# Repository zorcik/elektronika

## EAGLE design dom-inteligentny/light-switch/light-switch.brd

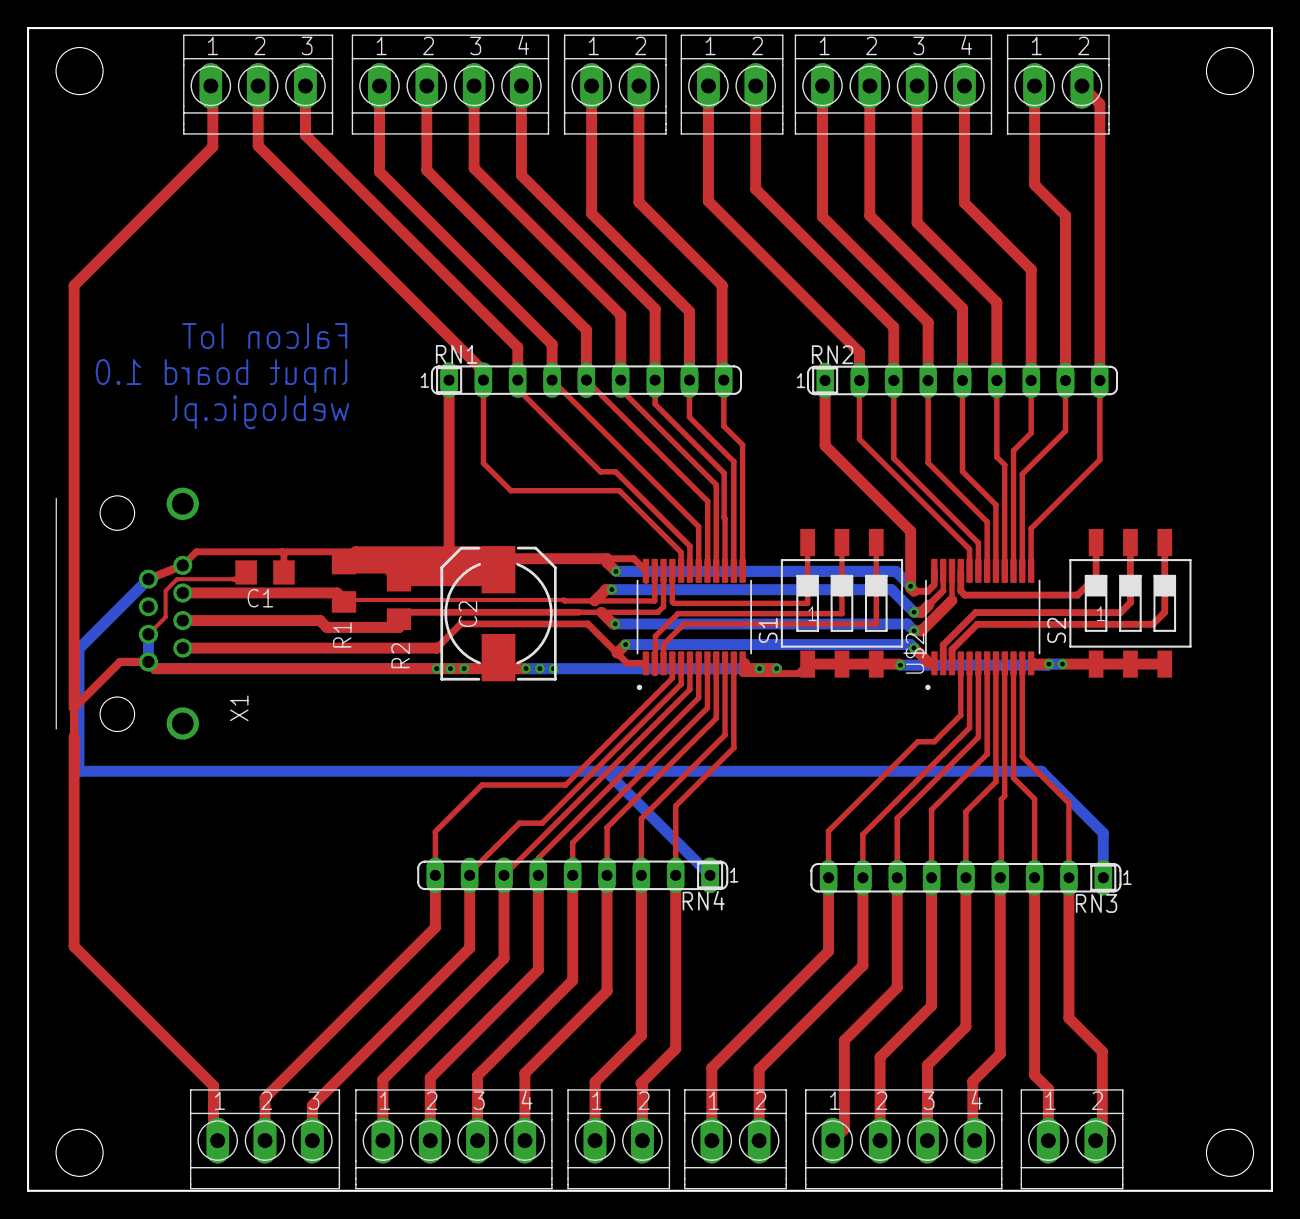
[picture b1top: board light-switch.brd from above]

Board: 2 copper layers, 92.0 x 86.0 mm, 25 parts (0 on the bottom side), 43 nets.

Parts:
C1: C1206
C2: 150CLZ-0810
R1, R2: R1206
RN1, RN2, RN3, RN4: SIL9
S1, S2: SWS003; SMS-003
U$1, U$2: PCF8575CSSOP24; SOP65P775X200-24N
X1: GLX-S-88M
X2, X3: TERMINAL-BLOCK-3.5MM-3-PIN-LONG-PAD; TERMINAL-BLOCK-3-PIN-3.5MM-LONG-PAD
X4, X6, X10, X11: TERMINAL-BLOCK-3.5MM-4-PIN-LONG-PAD; TERMINAL-BLOCK-4-PIN-3.5MM-LONG-PAD
X5, X7, X8, X9, X12, X13: TERMINAL-BLOCK-3.5MM-2-PIN-LONG-PAD; TERMINAL-BLOCK-2-PIN-3.5MM-LONG-PAD

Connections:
GND: C1.1, C2.-, S1.1, S1.2, S1.3, S2.1, S2.2, S2.3, U$1.12, U$2.12, X1.1, X1.3, X2.1, X3.1
INT: U$1.1, U$2.1, X1.2
unnamed: RN1.2, U$1.20, X3.2
unnamed: RN1.3, U$1.19, X3.3
unnamed: RN1.4, U$1.18, X4.1
unnamed: RN1.5, U$1.17, X4.2
unnamed: RN1.6, U$1.16, X4.3
unnamed: RN1.7, U$1.15, X4.4
unnamed: RN1.8, U$1.14, X5.1
unnamed: RN1.9, U$1.13, X5.2
unnamed: RN4.9, U$1.4, X2.2
unnamed: RN4.8, U$1.5, X2.3
unnamed: RN4.7, U$1.6, X6.1
unnamed: RN4.6, U$1.7, X6.2
unnamed: RN4.5, U$1.8, X6.3
unnamed: RN4.4, U$1.9, X6.4
unnamed: RN4.3, U$1.10, X7.1
unnamed: RN4.2, U$1.11, X7.2
unnamed: RN3.9, U$2.4, X9.1
unnamed: S1.4, U$1.3
unnamed: S2.5, U$2.2
unnamed: S1.6, U$1.21
unnamed: S1.5, U$1.2
unnamed: S2.4, U$2.3
unnamed: RN2.2, U$2.20, X8.1
unnamed: RN2.3, U$2.19, X8.2
unnamed: RN2.4, U$2.18, X10.1
unnamed: RN2.5, U$2.17, X10.2
unnamed: RN2.6, U$2.16, X10.3
unnamed: RN2.7, U$2.15, X10.4
unnamed: RN2.8, U$2.14, X12.1
unnamed: RN2.9, U$2.13, X12.2
unnamed: RN3.8, U$2.5, X9.2
unnamed: RN3.7, U$2.6, X11.1
unnamed: RN3.6, U$2.7, X11.2
unnamed: RN3.5, U$2.8, X11.3
unnamed: RN3.4, U$2.9, X11.4
unnamed: RN3.3, U$2.10, X13.1
unnamed: RN3.2, U$2.11, X13.2
unnamed: S2.6, U$2.21
SCL: R2.1, U$1.22, U$2.22, X1.4
SDA: R1.1, U$1.23, U$2.23, X1.6
VDD: C1.2, C2.+, R1.2, R2.2, RN1.1, RN2.1, RN3.1, RN4.1, U$1.24, U$2.24, X1.7, X1.8

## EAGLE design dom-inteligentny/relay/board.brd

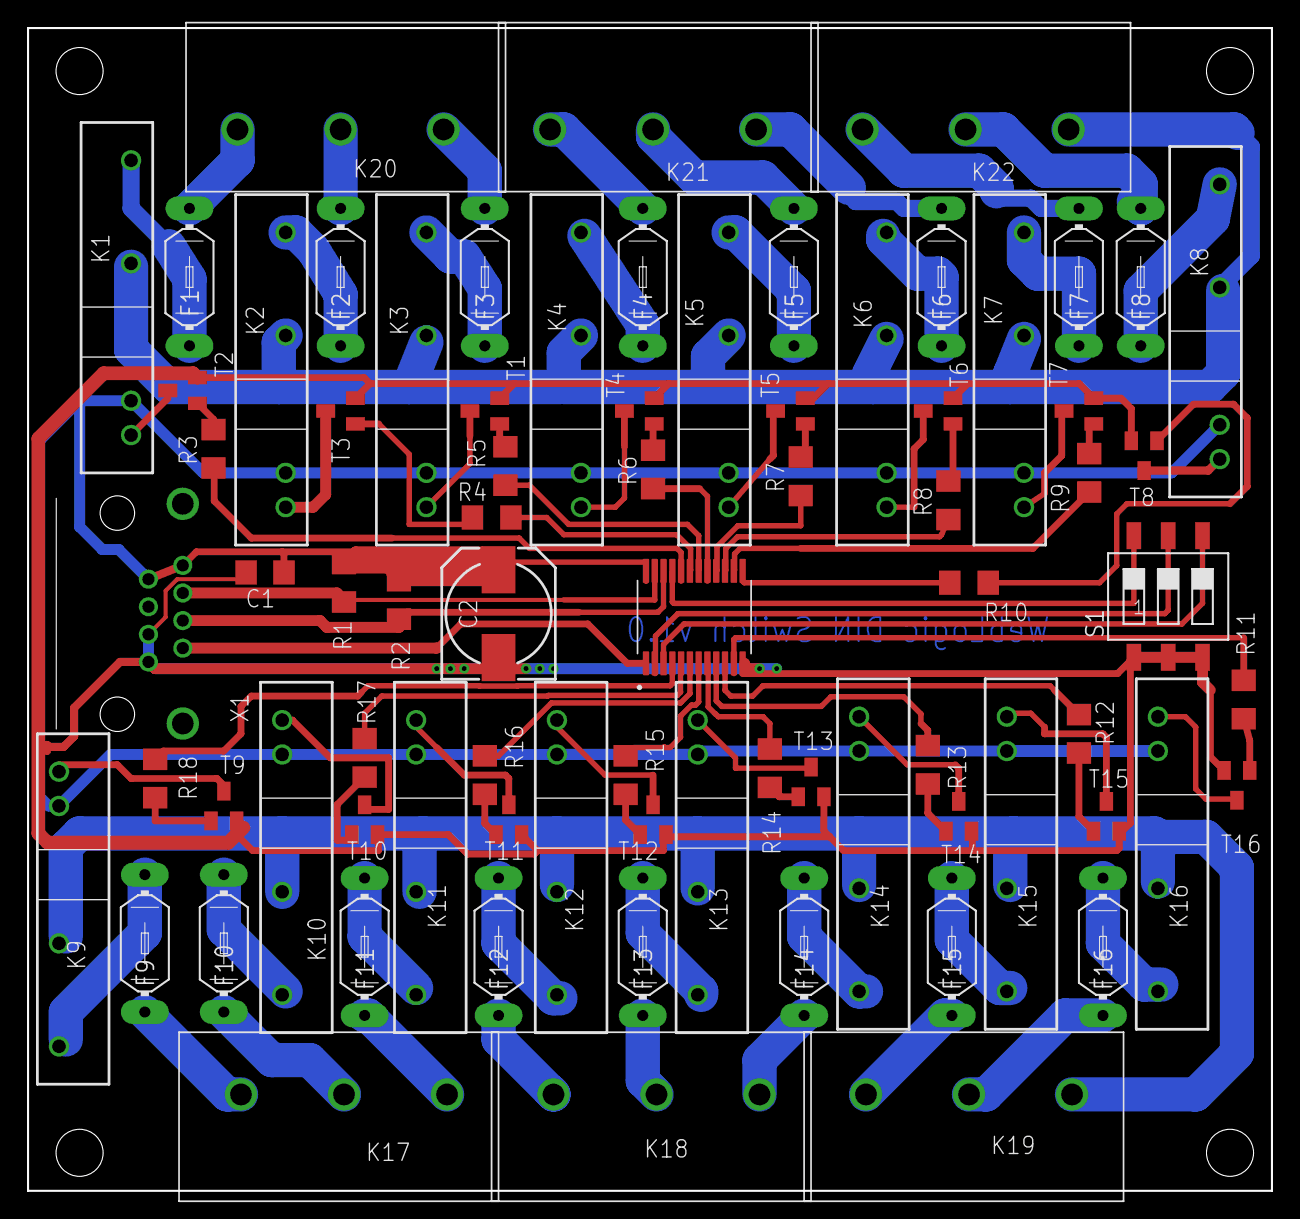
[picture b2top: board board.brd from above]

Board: 2 copper layers, 92.0 x 86.0 mm, 77 parts (0 on the bottom side), 90 nets.

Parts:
C1: C1206
C2: 150CLZ-0810
F1, F2, F3, F4, F5, F6, F7, F8, F9, F10, F11, F12, F13, F14, F15, F16: FUSELITTLEFUSE; LITTLEFUSE
K1, K2, K3, K4, K5, K6, K7, K8, K9, K10, K11, K12, K13, K14, K15, K16: OMRON-G3MB-202P-SSR
K17, K18, K19, K20, K21, K22: 691218410003
R1, R2, R3, R4, R5, R6, R7, R8, R9, R10, R11, R12, R13, R14, R15, R16, R17, R18: R1206
S1: SWS003; SMS-003
T1, T2, T3, T4, T5, T6, T7, T8, T9, T10, T11, T12, T13, T14, T15, T16: BC847; SOT23
U$1: PCF8575CSSOP24; SOP65P775X200-24N
X1: GLX-S-88M

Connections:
GND: C1.1, C2.-, S1.1, S1.2, S1.3, T1.2, T2.2, T3.2, T4.2, T5.2, T6.2, T7.2, T8.2, T9.2, T10.2, T11.2, T12.2, T13.2, T14.2, T15.2, T16.2, U$1.12, X1.1, X1.3
unnamed: F16.2, K16.1
unnamed: U$1.1, X1.2
unnamed: R3.1, U$1.20
unnamed: R4.1, U$1.19
unnamed: R18.2, T9.1
unnamed: R5.1, U$1.18
unnamed: R6.1, U$1.17
unnamed: R7.1, U$1.16
unnamed: R8.1, U$1.15
unnamed: R9.1, U$1.14
unnamed: R10.1, U$1.13
unnamed: R11.1, U$1.11
unnamed: R12.1, U$1.10
unnamed: R13.1, U$1.9
unnamed: R14.1, U$1.8
unnamed: R15.1, U$1.7
unnamed: R16.1, U$1.6
unnamed: R17.1, U$1.5
unnamed: R2.1, U$1.22, X1.4
unnamed: S1.4, U$1.3
unnamed: R1.1, U$1.23, X1.6
unnamed: K9.2, K10.2, K11.2, K12.2, K13.2, K14.2, K15.2, K16.2, K19.3
unnamed: F13.2, K13.1
unnamed: F14.1, K18.3
unnamed: F10.1, K17.2
unnamed: F11.1, K17.3
unnamed: S1.6, U$1.21
unnamed: S1.5, U$1.2
unnamed: C1.2, C2.+, K1.3, K2.3, K3.3, K4.3, K5.3, K6.3, K7.3, K8.3, K9.3, K10.3, K11.3, K12.3, K13.3, K14.3, K15.3, K16.3, R1.2, R2.2, U$1.24, X1.7, X1.8
unnamed: F9.1, K17.1
unnamed: F1.1, K1.1
unnamed: F2.1, K2.1
unnamed: F12.1, K18.1
unnamed: F3.1, K3.1
unnamed: F4.1, K4.1
unnamed: F15.1, K19.1
unnamed: F5.1, K5.1
unnamed: K1.2, K2.2, K3.2, K4.2, K5.2, K6.2, K7.2, K8.2, K22.1
unnamed: F8.2, K22.2
unnamed: F7.2, K22.3
unnamed: F6.2, K21.1
unnamed: F5.2, K21.2
unnamed: F4.2, K21.3
unnamed: F3.2, K20.1
unnamed: F6.1, K6.1
unnamed: F1.2, K20.3
unnamed: F7.1, K7.1
unnamed: F8.1, K8.1
unnamed: F9.2, K9.1
unnamed: F2.2, K20.2
unnamed: F10.2, K10.1
unnamed: F11.2, K11.1
unnamed: F12.2, K12.1
unnamed: F14.2, K14.1
unnamed: F15.2, K15.1
unnamed: F16.1, K19.2
unnamed: F13.1, K18.2
unnamed: R18.1, U$1.4
unnamed: R3.2, T2.1
unnamed: K1.4, T2.3
unnamed: R4.2, T3.1
unnamed: K2.4, T3.3
unnamed: R5.2, T1.1
unnamed: R6.2, T4.1
unnamed: R7.2, T5.1
unnamed: R8.2, T6.1
unnamed: R9.2, T7.1
unnamed: R10.2, T8.1
unnamed: K8.4, T8.3
unnamed: K7.4, T7.3
unnamed: K6.4, T6.3
unnamed: K5.4, T5.3
unnamed: R17.2, T10.1
unnamed: K4.4, T4.3
unnamed: K3.4, T1.3
unnamed: K9.4, T9.3
unnamed: K10.4, T10.3
unnamed: K11.4, T11.3
unnamed: R16.2, T11.1
unnamed: R11.2, T16.1
unnamed: R12.2, T15.1
unnamed: R13.2, T14.1
unnamed: R14.2, T13.1
unnamed: R15.2, T12.1
unnamed: K16.4, T16.3
unnamed: K15.4, T15.3
unnamed: K14.4, T14.3
unnamed: K13.4, T13.3
unnamed: K12.4, T12.3

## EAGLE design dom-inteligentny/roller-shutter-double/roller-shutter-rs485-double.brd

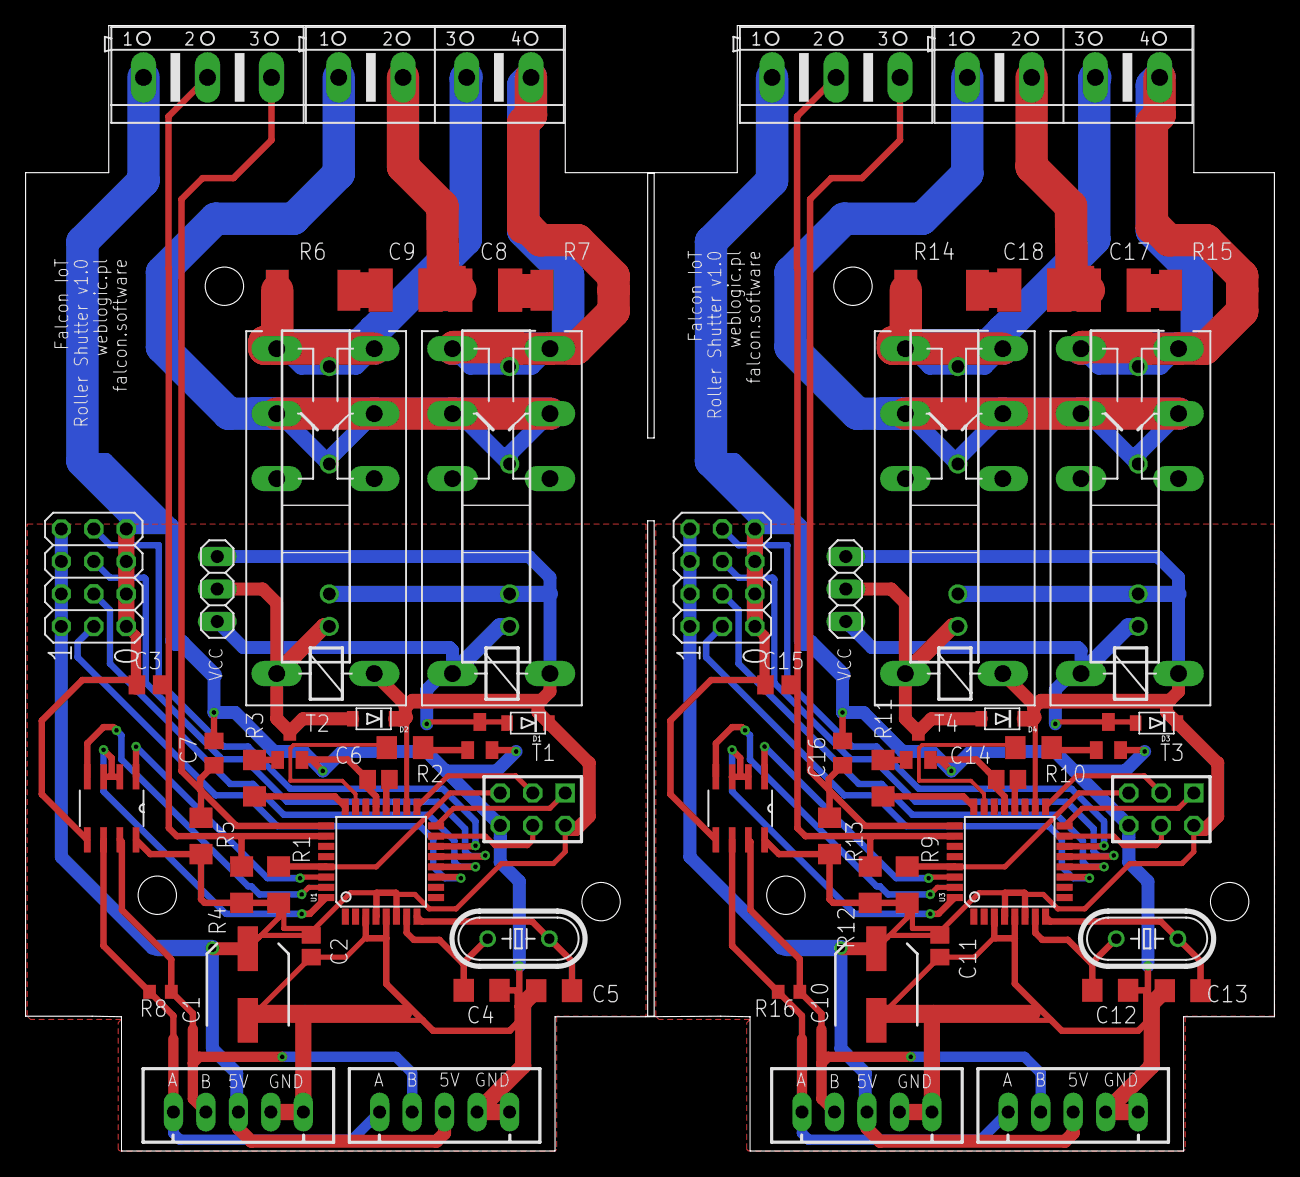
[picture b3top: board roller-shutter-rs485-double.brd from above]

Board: 2 copper layers, 97.6 x 88.0 mm, 70 parts (0 on the bottom side), 64 nets.

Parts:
C1, C10: SANYO-OSCON_SMD_C6
C2, C6, C11, C14: 0.1uF; C0805
C3, C7, C15, C16: C0805
C4, C5, C12, C13: 22pF; C1206
C8, C9, C17, C18: C1812
D1, D2, D3, D4: SOD-123FL
JP1, JP3: AVR-ISP-6
JP2, JP4: 1X03
JP5, JP6: 3X04
K1, K4, K5, K6: RP421110; RP420
K2, K3, K7, K8: OMRON-G3MB-202P-SSR
Q1, Q2: 16MHz; HC49/S
R1, R9: 10K; R1206
R2, R3, R4, R5, R10, R11, R12, R13: R1206
R6, R7, R14, R15: R2512
R8, R16: 120R; R0603
T1, T2, T3, T4: BC847; SOT23
U1, U3: ATMEGA328; TQFP32-08
U2, U4: MAX487ESA+TCBX; SOIC127P600X175-8N
X1, X2, X3, X6: JST-XH-05-PIN-LONG-PAD; JST-XH-05-PACKAGE-LONG-PAD
X4, X7: AK500/3
X5, X8: AK500/4

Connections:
A: R8.2, U2.6, X2.1, X3.1
A0: R2.1, U1.23
A1: R3.1, U1.24
A2: C7.2, R5.1, U1.25, X4.3
A3: C3.2, R4.1, U1.26, X4.2
A4: R10.1, U3.23
A5: R11.1, U3.24
A8: C16.2, R13.1, U3.25, X7.3
A9: C15.2, R12.1, U3.26, X7.2
A12: R16.2, U4.6, X1.1, X6.1
AREF: C6.1, U1.20
AREF1: C14.1, U3.20
B: R8.1, U2.7, X2.2, X3.2
B1: R16.1, U4.7, X1.2, X6.2
D0: U1.30, U2.1
D1: U1.31, U2.4
D2: U1.32, U2.2, U2.3
D7: JP6.11, U1.11
D8: JP6.8, U1.12
D9: JP6.5, U1.13
D10: JP6.2, U1.14
D11: JP1.4, U1.15
D12: JP1.1, U1.16
D13: JP1.3, U1.17
D14: U3.30, U4.1
D15: U3.31, U4.4
D16: U3.32, U4.2, U4.3
D21: JP5.11, U3.11
D22: JP5.8, U3.12
D23: JP5.5, U3.13
D24: JP5.2, U3.14
D25: JP3.4, U3.15
D26: JP3.1, U3.16
D27: JP3.3, U3.17
GND: C1.-, C2.2, C3.1, C4.2, C5.2, C6.2, C7.1, JP1.6, JP6.3, JP6.6, JP6.9, JP6.12, T1.2, T2.2, U1.3, U1.5, U1.21, U2.5, X2.4, X2.5, X3.4, X3.5, X4.1
GND1: C10.-, C11.2, C12.2, C13.2, C14.2, C15.1, C16.1, JP3.6, JP5.3, JP5.6, JP5.9, JP5.12, T3.2, T4.2, U3.3, U3.5, U3.21, U4.5, X1.4, X1.5, X6.4, X6.5, X7.1
unnamed: D1.A, JP2.1, K1.A2, K2.4, T1.3
unnamed: D2.A, JP2.2, K3.4, K4.A2, T2.3
unnamed: C12.1, Q2.2, U3.7
unnamed: K1.11, K1.21, K2.2, K3.2, K4.11, K4.21, X5.1
unnamed: R2.2, T1.1
unnamed: R3.2, T2.1
unnamed: K1.14, K1.24, K2.1, R7.2, X5.4
unnamed: K3.1, K4.14, K4.24, R6.2, X5.3
unnamed: C8.2, R7.1
unnamed: C9.2, R6.1
unnamed: C8.1, C9.1, X5.2
unnamed: C13.1, Q2.1, U3.8
unnamed: D3.A, JP4.1, K5.A2, K7.4, T3.3
unnamed: D4.A, JP4.2, K6.A2, K8.4, T4.3
unnamed: R10.2, T3.1
unnamed: R11.2, T4.1
unnamed: K5.11, K5.21, K6.11, K6.21, K7.2, K8.2, X8.1
unnamed: K5.14, K5.24, K7.1, R15.2, X8.4
unnamed: K6.14, K6.24, K8.1, R14.2, X8.3
unnamed: C17.2, R15.1
unnamed: C18.2, R14.1
unnamed: C17.1, C18.1, X8.2
unnamed: C4.1, Q1.2, U1.7
unnamed: C5.1, Q1.1, U1.8
RST: JP1.5, R1.1, U1.29
RST1: JP3.5, R9.1, U3.29
VCC: C1.+, C2.1, D1.C, D2.C, JP1.2, JP2.3, JP6.1, JP6.4, JP6.7, JP6.10, K1.A1, K2.3, K3.3, K4.A1, R1.2, R4.2, R5.2, U1.4, U1.6, U1.18, U2.8, X2.3, X3.3
VCC1: C10.+, C11.1, D3.C, D4.C, JP3.2, JP4.3, JP5.1, JP5.4, JP5.7, JP5.10, K5.A1, K6.A1, K7.3, K8.3, R9.2, R12.2, R13.2, U3.4, U3.6, U3.18, U4.8, X1.3, X6.3

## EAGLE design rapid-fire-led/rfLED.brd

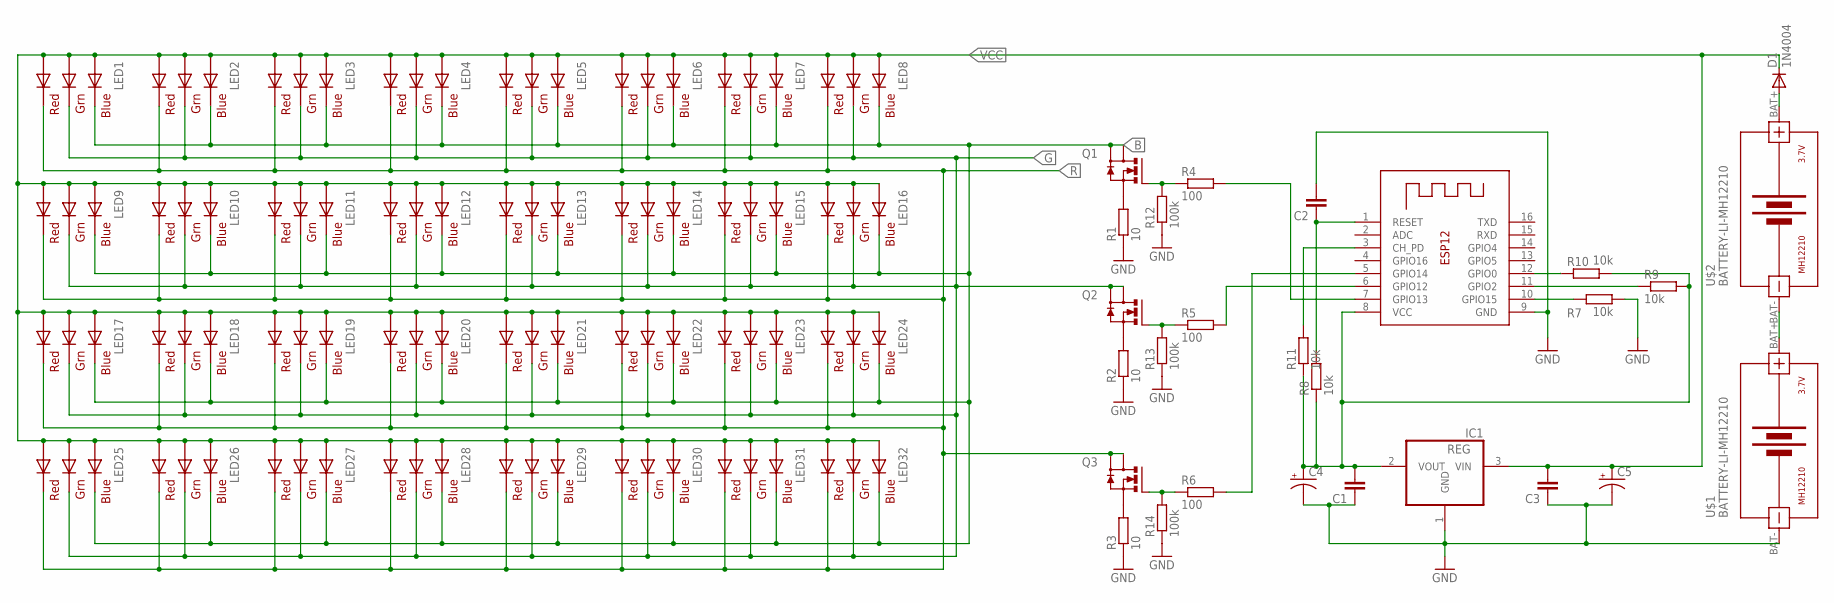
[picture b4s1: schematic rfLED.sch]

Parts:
C1, C2, C3: C; C0805
C4, C5: CPOL-US150CLZ-1010; 150CLZ-1010
D1: 1N4004; DO41-10
IC1: REG; SOT223
LED1, LED2, LED3, LED4, LED5, LED6, LED7, LED8, LED9, LED10, LED11, LED12, LED13, LED14, LED15, LED16, LED17, LED18, LED19, LED20, LED21, LED22, LED23, LED24, LED25, LED26, LED27, LED28, LED29, LED30, LED31, LED32: RGBLED5050
Q1, Q2, Q3: MOSFET_N_SOT223; SOT223
R1, R2, R3: 10; R2512
R4, R5, R6: 100; R1206
R7, R8, R9, R10, R11: 10k; R1206
R12, R13, R14: 100k; R1206
U$1, U$2: BATTERY-LI-MH12210
X1: ESP-12

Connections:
B: LED1.4 (BLUE_C), LED2.4 (BLUE_C), LED3.4 (BLUE_C), LED4.4 (BLUE_C), LED5.4 (BLUE_C), LED6.4 (BLUE_C), LED7.4 (BLUE_C), LED8.4 (BLUE_C), LED9.4 (BLUE_C), LED10.4 (BLUE_C), LED11.4 (BLUE_C), LED12.4 (BLUE_C), LED13.4 (BLUE_C), LED14.4 (BLUE_C), LED15.4 (BLUE_C), LED16.4 (BLUE_C), LED17.4 (BLUE_C), LED18.4 (BLUE_C), LED19.4 (BLUE_C), LED20.4 (BLUE_C), LED21.4 (BLUE_C), LED22.4 (BLUE_C), LED23.4 (BLUE_C), LED24.4 (BLUE_C), LED25.4 (BLUE_C), LED26.4 (BLUE_C), LED27.4 (BLUE_C), LED28.4 (BLUE_C), LED29.4 (BLUE_C), LED30.4 (BLUE_C), LED31.4 (BLUE_C), LED32.4 (BLUE_C), Q1.2 (D), Q1.4 (D1)
G: LED1.6 (GREEN_C), LED2.6 (GREEN_C), LED3.6 (GREEN_C), LED4.6 (GREEN_C), LED5.6 (GREEN_C), LED6.6 (GREEN_C), LED7.6 (GREEN_C), LED8.6 (GREEN_C), LED9.6 (GREEN_C), LED10.6 (GREEN_C), LED11.6 (GREEN_C), LED12.6 (GREEN_C), LED13.6 (GREEN_C), LED14.6 (GREEN_C), LED15.6 (GREEN_C), LED16.6 (GREEN_C), LED17.6 (GREEN_C), LED18.6 (GREEN_C), LED19.6 (GREEN_C), LED20.6 (GREEN_C), LED21.6 (GREEN_C), LED22.6 (GREEN_C), LED23.6 (GREEN_C), LED24.6 (GREEN_C), LED25.6 (GREEN_C), LED26.6 (GREEN_C), LED27.6 (GREEN_C), LED28.6 (GREEN_C), LED29.6 (GREEN_C), LED30.6 (GREEN_C), LED31.6 (GREEN_C), LED32.6 (GREEN_C), Q2.2 (D), Q2.4 (D1)
GND: C1.1, C2.2, C3.1, C4.-, C5.-, IC1.1 (GND), R1.1, R2.1, R3.1, R7.2, R12.1, R13.1, R14.1, U$1.BAT-, X1.9 (GND)
unnamed: Q1.3 (S), R1.2
unnamed: Q2.3 (S), R2.2
unnamed: Q3.3 (S), R3.2
unnamed: Q1.1 (G), R4.1, R12.2
unnamed: Q2.1 (G), R5.1, R13.2
unnamed: Q3.1 (G), R6.1, R14.2
unnamed: R5.2, X1.6 (GPIO12)
unnamed: C1.2, C4.+, IC1.2 (VOUT), R8.1, R9.2, R10.2, R11.1, X1.8 (VCC)
unnamed: R6.2, X1.5 (GPIO14)
unnamed: R4.2, X1.7 (GPIO13)
unnamed: R7.1, X1.10 (GPIO15)
unnamed: U$1.BAT+, U$2.BAT-
unnamed: C2.1, R8.2, X1.1 (RESET)
unnamed: R10.1, X1.12 (GPIO0)
unnamed: R9.1, X1.11 (GPIO2)
unnamed: D1.A, U$2.BAT+
unnamed: R11.2, X1.3 (CH_PD)
R: LED1.5 (RED_C), LED2.5 (RED_C), LED3.5 (RED_C), LED4.5 (RED_C), LED5.5 (RED_C), LED6.5 (RED_C), LED7.5 (RED_C), LED8.5 (RED_C), LED9.5 (RED_C), LED10.5 (RED_C), LED11.5 (RED_C), LED12.5 (RED_C), LED13.5 (RED_C), LED14.5 (RED_C), LED15.5 (RED_C), LED16.5 (RED_C), LED17.5 (RED_C), LED18.5 (RED_C), LED19.5 (RED_C), LED20.5 (RED_C), LED21.5 (RED_C), LED22.5 (RED_C), LED23.5 (RED_C), LED24.5 (RED_C), LED25.5 (RED_C), LED26.5 (RED_C), LED27.5 (RED_C), LED28.5 (RED_C), LED29.5 (RED_C), LED30.5 (RED_C), LED31.5 (RED_C), LED32.5 (RED_C), Q3.2 (D), Q3.4 (D1)
VCC: C3.2, C5.+, D1.C, IC1.3 (VIN), LED1.1 (GREEN_A), LED1.2 (RED_A), LED1.3 (BLUE_A), LED2.1 (GREEN_A), LED2.2 (RED_A), LED2.3 (BLUE_A), LED3.1 (GREEN_A), LED3.2 (RED_A), LED3.3 (BLUE_A), LED4.1 (GREEN_A), LED4.2 (RED_A), LED4.3 (BLUE_A), LED5.1 (GREEN_A), LED5.2 (RED_A), LED5.3 (BLUE_A), LED6.1 (GREEN_A), LED6.2 (RED_A), LED6.3 (BLUE_A), LED7.1 (GREEN_A), LED7.2 (RED_A), LED7.3 (BLUE_A), LED8.1 (GREEN_A), LED8.2 (RED_A), LED8.3 (BLUE_A), LED9.1 (GREEN_A), LED9.2 (RED_A), LED9.3 (BLUE_A), LED10.1 (GREEN_A), LED10.2 (RED_A), LED10.3 (BLUE_A), LED11.1 (GREEN_A), LED11.2 (RED_A), LED11.3 (BLUE_A), LED12.1 (GREEN_A), LED12.2 (RED_A), LED12.3 (BLUE_A), LED13.1 (GREEN_A), LED13.2 (RED_A), LED13.3 (BLUE_A), LED14.1 (GREEN_A), LED14.2 (RED_A), LED14.3 (BLUE_A), LED15.1 (GREEN_A), LED15.2 (RED_A), LED15.3 (BLUE_A), LED16.1 (GREEN_A), LED16.2 (RED_A), LED16.3 (BLUE_A), LED17.1 (GREEN_A), LED17.2 (RED_A), LED17.3 (BLUE_A), LED18.1 (GREEN_A), LED18.2 (RED_A), LED18.3 (BLUE_A), LED19.1 (GREEN_A), LED19.2 (RED_A), LED19.3 (BLUE_A), LED20.1 (GREEN_A), LED20.2 (RED_A), LED20.3 (BLUE_A), LED21.1 (GREEN_A), LED21.2 (RED_A), LED21.3 (BLUE_A), LED22.1 (GREEN_A), LED22.2 (RED_A), LED22.3 (BLUE_A), LED23.1 (GREEN_A), LED23.2 (RED_A), LED23.3 (BLUE_A), LED24.1 (GREEN_A), LED24.2 (RED_A), LED24.3 (BLUE_A), LED25.1 (GREEN_A), LED25.2 (RED_A), LED25.3 (BLUE_A), LED26.1 (GREEN_A), LED26.2 (RED_A), LED26.3 (BLUE_A), LED27.1 (GREEN_A), LED27.2 (RED_A), LED27.3 (BLUE_A), LED28.1 (GREEN_A), LED28.2 (RED_A), LED28.3 (BLUE_A), LED29.1 (GREEN_A), LED29.2 (RED_A), LED29.3 (BLUE_A), LED30.1 (GREEN_A), LED30.2 (RED_A), LED30.3 (BLUE_A), LED31.1 (GREEN_A), LED31.2 (RED_A), LED31.3 (BLUE_A), LED32.1 (GREEN_A), LED32.2 (RED_A), LED32.3 (BLUE_A)

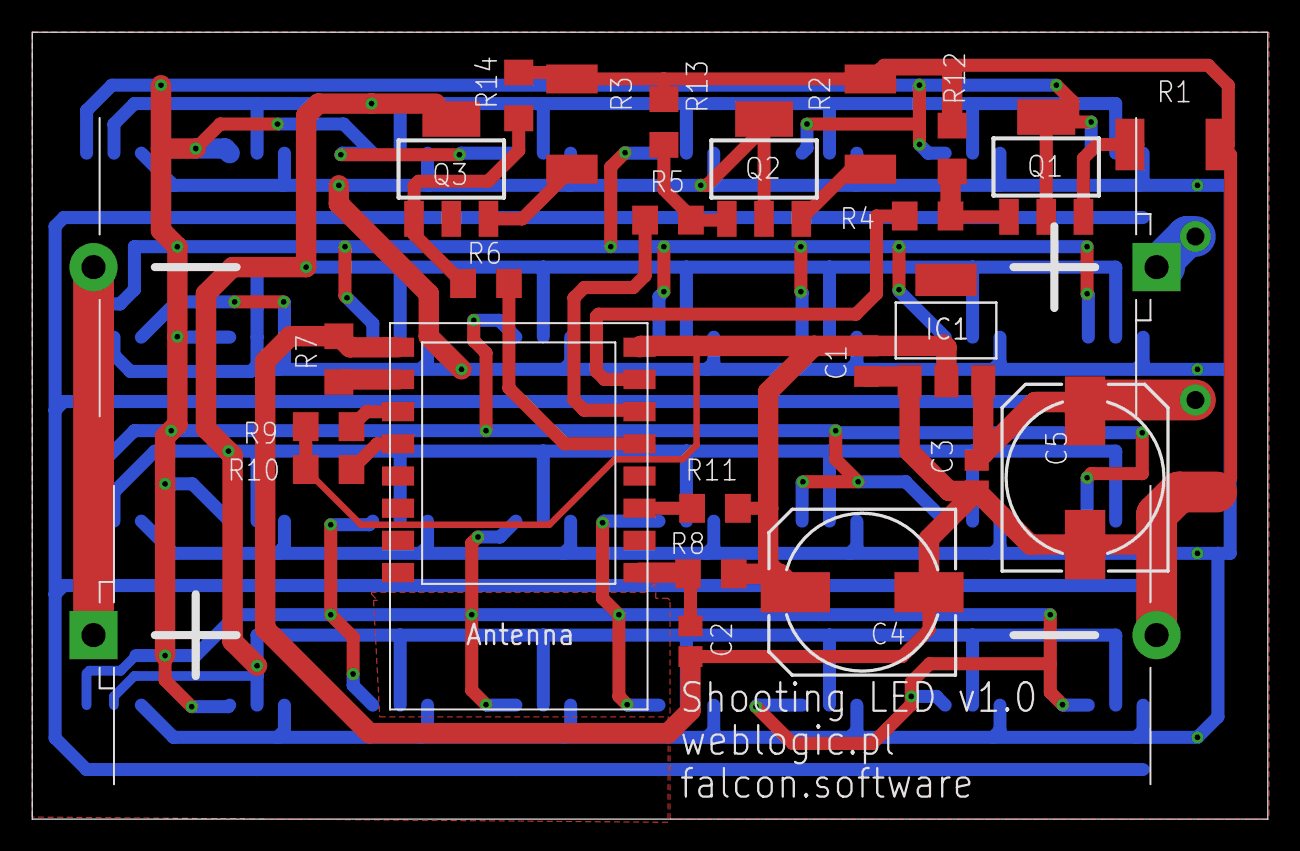
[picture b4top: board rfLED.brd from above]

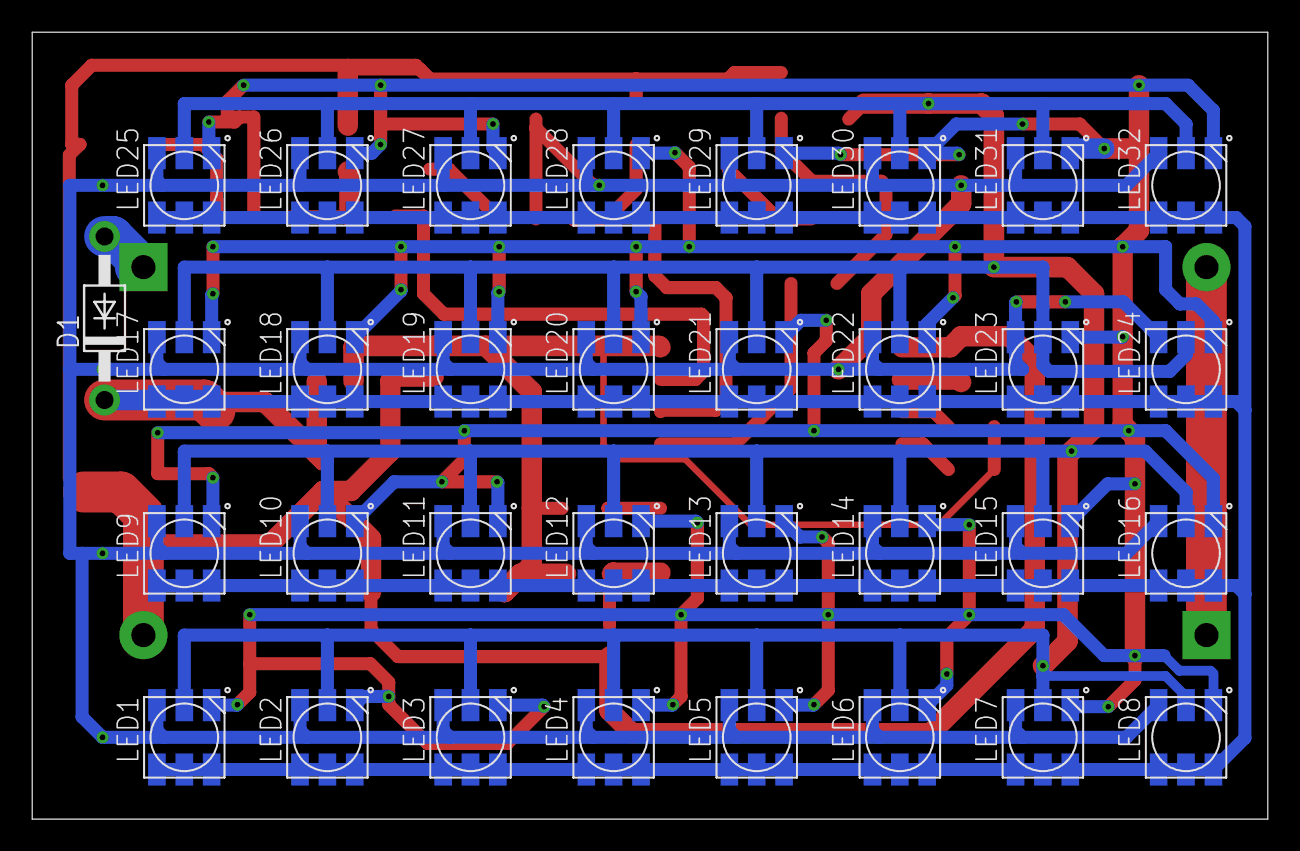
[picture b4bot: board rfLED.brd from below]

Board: 2 copper layers, 76.8 x 48.9 mm, 59 parts (33 on the bottom side), 22 nets.

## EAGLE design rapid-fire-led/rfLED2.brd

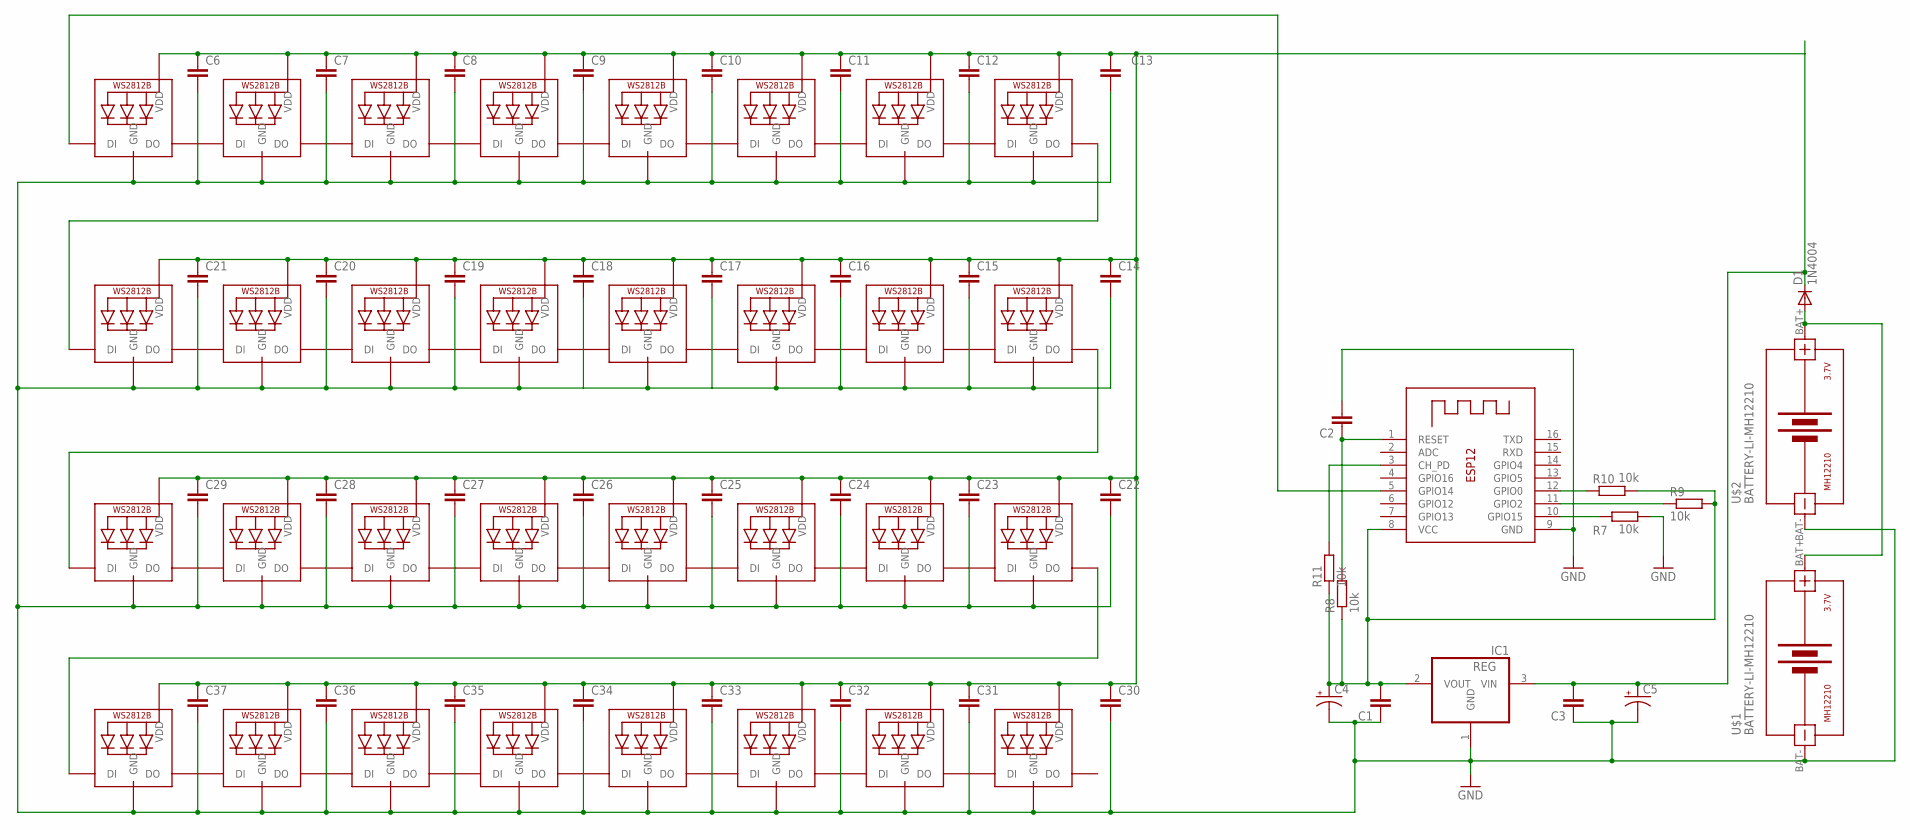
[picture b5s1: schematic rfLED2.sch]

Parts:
C1, C2, C3, C6, C7, C8, C9, C10, C11, C12, C13, C14, C15, C16, C17, C18, C19, C20, C21, C22, C23, C24, C25, C26, C27, C28, C29, C30, C31, C32, C33, C34, C35, C36, C37: C; C0805
C4, C5: CPOL-US150CLZ-1010; 150CLZ-1010
D1: 1N4004; DO41-10
IC1: REG; SOT223
LED1, LED2, LED3, LED4, LED5, LED6, LED7, LED8, LED9, LED10, LED11, LED12, LED13, LED14, LED15, LED16, LED17, LED18, LED19, LED20, LED21, LED22, LED23, LED24, LED25, LED26, LED27, LED28, LED29, LED30, LED31, LED32: WS2812B5050; WS2812B
R7, R8, R9, R10, R11: 10k; R1206
U$1, U$2: BATTERY-LI-MH12210
X1: ESP-12

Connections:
GND: C1.1, C2.2, C3.1, C4.-, C5.-, C6.2, C7.2, C8.2, C9.2, C10.2, C11.2, C12.2, C13.2, C14.2, C15.2, C16.2, C17.2, C18.2, C19.2, C20.2, C21.2, C22.2, C23.2, C24.2, C25.2, C26.2, C27.2, C28.2, C29.2, C30.2, C31.2, C32.2, C33.2, C34.2, C35.2, C36.2, C37.2, IC1.1 (GND), LED1.3-GND (GND), LED2.3-GND (GND), LED3.3-GND (GND), LED4.3-GND (GND), LED5.3-GND (GND), LED6.3-GND (GND), LED7.3-GND (GND), LED8.3-GND (GND), LED9.3-GND (GND), LED10.3-GND (GND), LED11.3-GND (GND), LED12.3-GND (GND), LED13.3-GND (GND), LED14.3-GND (GND), LED15.3-GND (GND), LED16.3-GND (GND), LED17.3-GND (GND), LED18.3-GND (GND), LED19.3-GND (GND), LED20.3-GND (GND), LED21.3-GND (GND), LED22.3-GND (GND), LED23.3-GND (GND), LED24.3-GND (GND), LED25.3-GND (GND), LED26.3-GND (GND), LED27.3-GND (GND), LED28.3-GND (GND), LED29.3-GND (GND), LED30.3-GND (GND), LED31.3-GND (GND), LED32.3-GND (GND), R7.2, U$1.BAT-, U$2.BAT-, X1.9 (GND)
unnamed: LED1.2-DOUT (DO), LED2.4-DIN (DI)
unnamed: LED2.2-DOUT (DO), LED3.4-DIN (DI)
unnamed: LED3.2-DOUT (DO), LED4.4-DIN (DI)
unnamed: LED4.2-DOUT (DO), LED5.4-DIN (DI)
unnamed: LED5.2-DOUT (DO), LED6.4-DIN (DI)
unnamed: LED6.2-DOUT (DO), LED7.4-DIN (DI)
unnamed: LED7.2-DOUT (DO), LED8.4-DIN (DI)
unnamed: C1.2, C4.+, IC1.2 (VOUT), R8.1, R9.2, R10.2, R11.1, X1.8 (VCC)
unnamed: LED1.4-DIN (DI), X1.5 (GPIO14)
unnamed: R7.1, X1.10 (GPIO15)
unnamed: LED16.2-DOUT (DO), LED17.4-DIN (DI)
unnamed: C2.1, R8.2, X1.1 (RESET)
unnamed: R10.1, X1.12 (GPIO0)
unnamed: R9.1, X1.11 (GPIO2)
unnamed: D1.A, U$1.BAT+, U$2.BAT+
unnamed: R11.2, X1.3 (CH_PD)
unnamed: LED9.2-DOUT (DO), LED10.4-DIN (DI)
unnamed: LED10.2-DOUT (DO), LED11.4-DIN (DI)
unnamed: LED11.2-DOUT (DO), LED12.4-DIN (DI)
unnamed: LED12.2-DOUT (DO), LED13.4-DIN (DI)
unnamed: LED13.2-DOUT (DO), LED14.4-DIN (DI)
unnamed: LED14.2-DOUT (DO), LED15.4-DIN (DI)
unnamed: LED15.2-DOUT (DO), LED16.4-DIN (DI)
unnamed: LED17.2-DOUT (DO), LED18.4-DIN (DI)
unnamed: LED18.2-DOUT (DO), LED19.4-DIN (DI)
unnamed: LED19.2-DOUT (DO), LED20.4-DIN (DI)
unnamed: LED20.2-DOUT (DO), LED21.4-DIN (DI)
unnamed: LED21.2-DOUT (DO), LED22.4-DIN (DI)
unnamed: LED22.2-DOUT (DO), LED23.4-DIN (DI)
unnamed: LED23.2-DOUT (DO), LED24.4-DIN (DI)
unnamed: LED25.2-DOUT (DO), LED26.4-DIN (DI)
unnamed: LED26.2-DOUT (DO), LED27.4-DIN (DI)
unnamed: LED27.2-DOUT (DO), LED28.4-DIN (DI)
unnamed: LED28.2-DOUT (DO), LED29.4-DIN (DI)
unnamed: LED29.2-DOUT (DO), LED30.4-DIN (DI)
unnamed: LED30.2-DOUT (DO), LED31.4-DIN (DI)
unnamed: LED31.2-DOUT (DO), LED32.4-DIN (DI)
unnamed: LED8.2-DOUT (DO), LED9.4-DIN (DI)
unnamed: LED24.2-DOUT (DO), LED25.4-DIN (DI)
VCC: C3.2, C5.+, C6.1, C7.1, C8.1, C9.1, C10.1, C11.1, C12.1, C13.1, C14.1, C15.1, C16.1, C17.1, C18.1, C19.1, C20.1, C21.1, C22.1, C23.1, C24.1, C25.1, C26.1, C27.1, C28.1, C29.1, C30.1, C31.1, C32.1, C33.1, C34.1, C35.1, C36.1, C37.1, D1.C, IC1.3 (VIN), LED1.1-VDD (VDD), LED2.1-VDD (VDD), LED3.1-VDD (VDD), LED4.1-VDD (VDD), LED5.1-VDD (VDD), LED6.1-VDD (VDD), LED7.1-VDD (VDD), LED8.1-VDD (VDD), LED9.1-VDD (VDD), LED10.1-VDD (VDD), LED11.1-VDD (VDD), LED12.1-VDD (VDD), LED13.1-VDD (VDD), LED14.1-VDD (VDD), LED15.1-VDD (VDD), LED16.1-VDD (VDD), LED17.1-VDD (VDD), LED18.1-VDD (VDD), LED19.1-VDD (VDD), LED20.1-VDD (VDD), LED21.1-VDD (VDD), LED22.1-VDD (VDD), LED23.1-VDD (VDD), LED24.1-VDD (VDD), LED25.1-VDD (VDD), LED26.1-VDD (VDD), LED27.1-VDD (VDD), LED28.1-VDD (VDD), LED29.1-VDD (VDD), LED30.1-VDD (VDD), LED31.1-VDD (VDD), LED32.1-VDD (VDD)

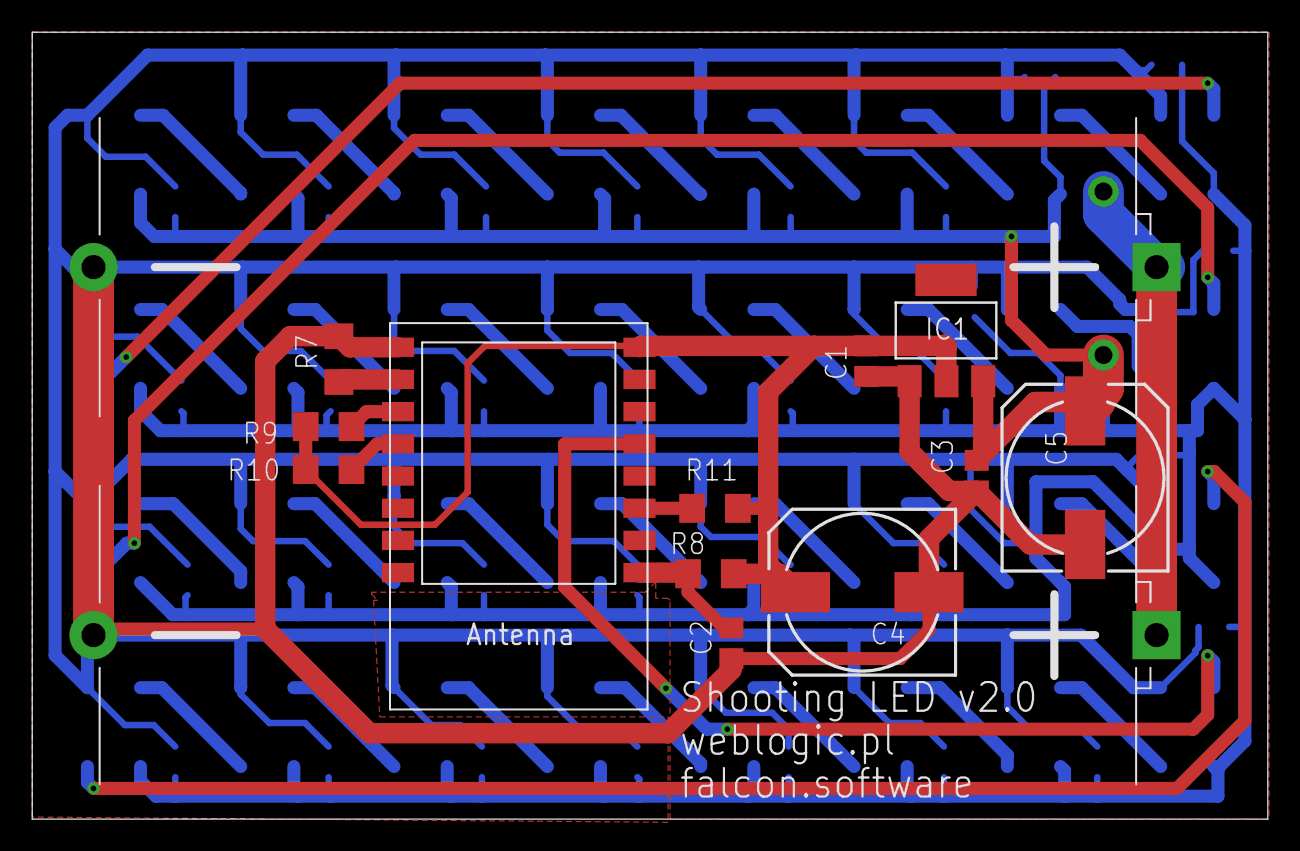
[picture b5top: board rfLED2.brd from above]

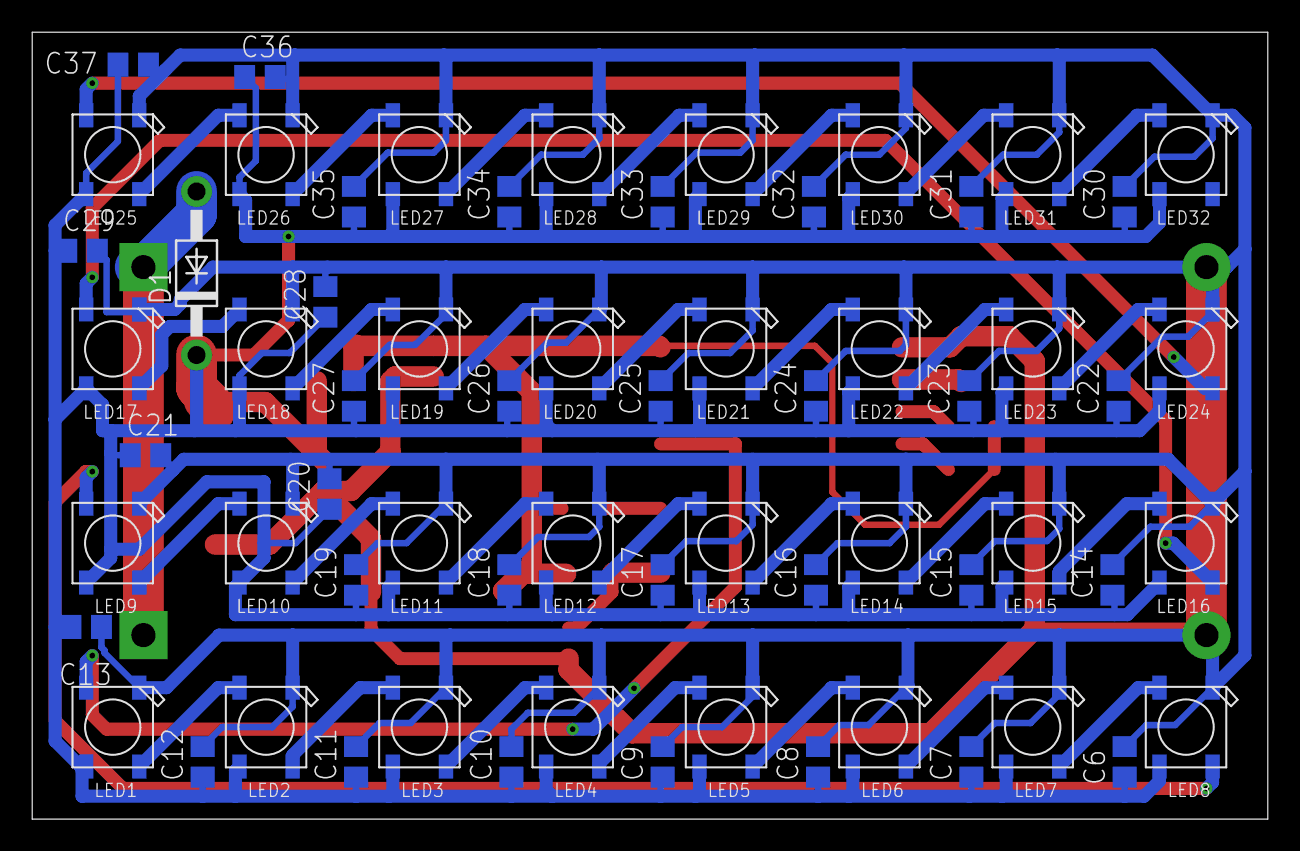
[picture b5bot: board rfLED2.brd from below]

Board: 2 copper layers, 76.8 x 48.9 mm, 79 parts (65 on the bottom side), 41 nets.

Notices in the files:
parts and their libraries:
Wurth_Elektronik_Electromechanic_Termina: Copyright: Würth Elektronik
m-pad-2.1: License : GNU General Public License version 2 (see bottom)
diy-modules: Released under the Creative Commons Attribution 4.0 International License: http://creativecommons.org/licenses/by/4.0
